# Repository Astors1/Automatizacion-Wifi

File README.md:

# Automatizacion wifi
Proyecto: Automatizaación WIFI Y infrarrojo. Alumnos: Alliana Facundo y Agustin Astorga ,con colaboracion de Alejo Guerra. Profesor: Martin Leguizamon. *Descripción del proyecto: Este dispositivo actúa como un control de tomacorrientes, donde se pueden agregar diferentes dispositivos, y permite apagarlos o prenderlos mediante una página web con interruptores. Además, cuenta con un sistema de control de seguridad (solo se puede activar manualmente)por infrarrojo, en caso de que no sea posible conectarse por WiFi. Objetivo: El objetivo principal es mejorar el control de dispositivos (luces, herramientas, etc.) de manera más práctica y permitir su manejo a distancia. En versiones anteriores, este dispositivo funcionaba mediante Bluetooth, lo que presentaba varias limitaciones: un alcance de solo 1 metro y la necesidad de instalar una aplicación en el teléfono móvil para su uso. En esta nueva versión, se mejorará la conexión a través de WiFi, lo que permitirá un mayor alcance y eliminará la necesidad de instalar aplicaciones adicionales, ya que funcionará mediante una dirección IP. Sin embargo, para situaciones en las que no se disponga de WiFi, el dispositivo contará con una opción de control por infrarrojos, que se podrá activar manualmente. Esta opción tendrá un alcance más limitado, pero ofrecerá una solución práctica y segura para su control. Listado de materiales/fuentes: • Microcontrolador ESP32/ (embebido reciclado) • Resistencias/optocopladores /transistores/pulsadores/rectificadores, etc (reciclados) • Relays x4 (reciclados) • Módulo infrarrojo (emisor/transmisor) ($8.000) • placa cobre doble faz (ya comprada) • Estaño, conectores, cables, etc ($10.000) Costo aproximado: $20.000.

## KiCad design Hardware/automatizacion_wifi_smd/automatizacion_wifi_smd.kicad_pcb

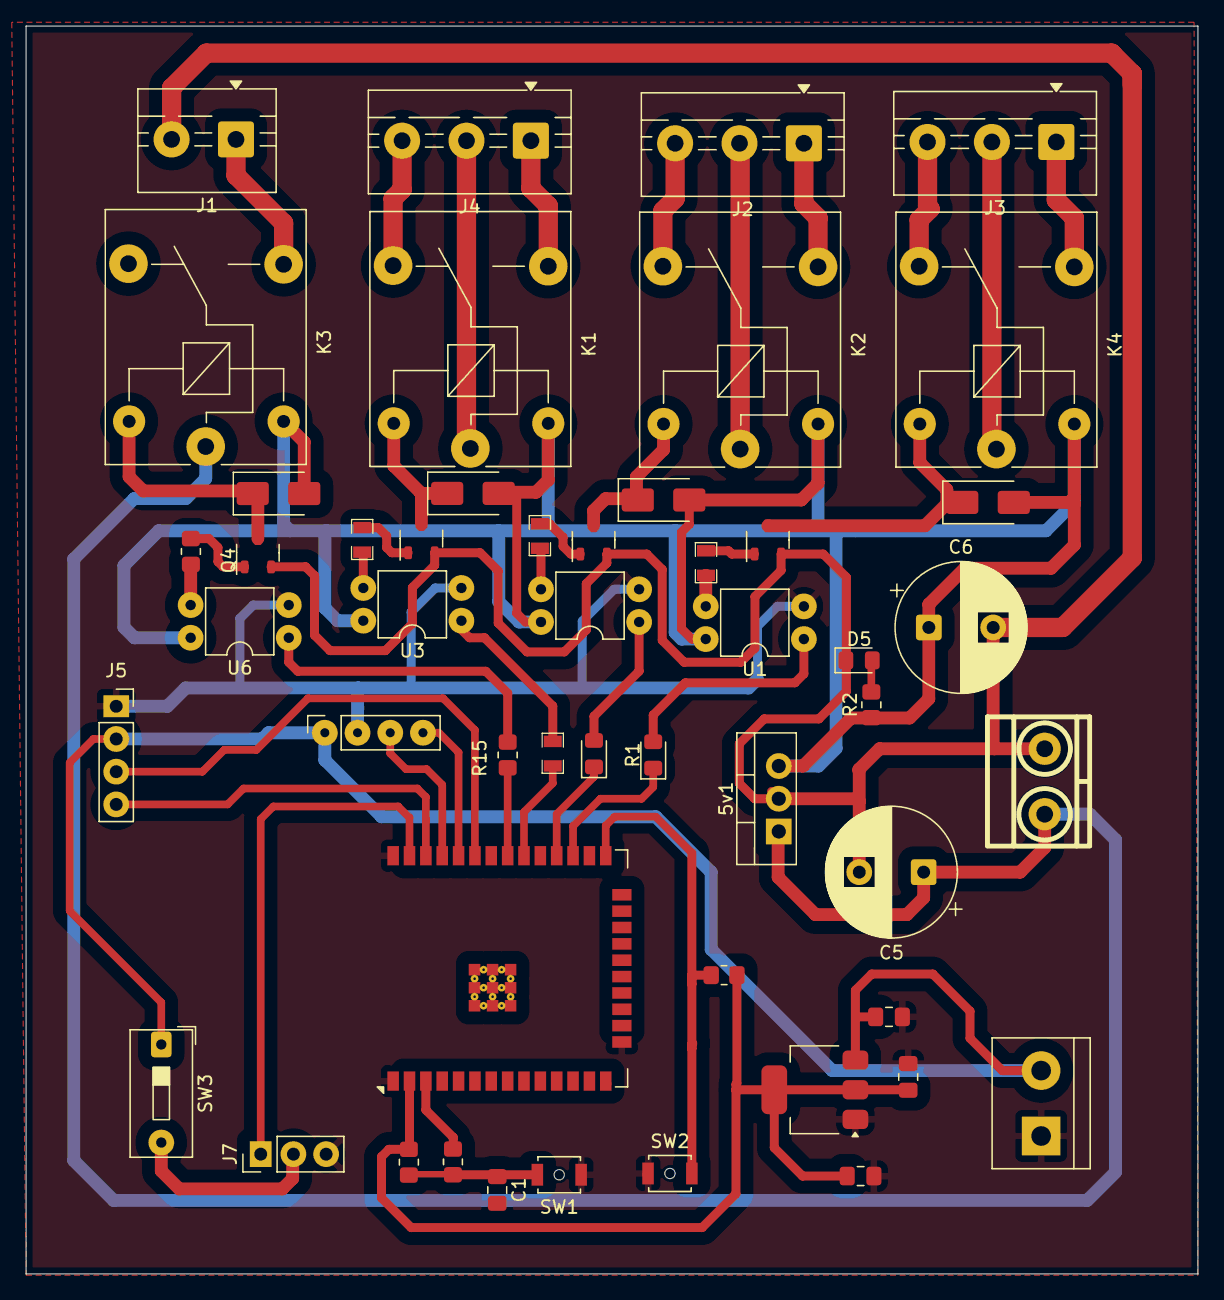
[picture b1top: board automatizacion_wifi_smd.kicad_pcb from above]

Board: 2 copper layers, 91.0 x 96.9 mm, 50 parts (0 on the bottom side), 46 nets.

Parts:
5v1: LM7805_TO220; TO-220-3_Vertical
C1: 100nF; C_0805_2012Metric_Pad1.18x1.45mm_HandSolder
C2, C4: 10 uF; C_0805_2012Metric_Pad1.18x1.45mm_HandSolder
C3: 100 nF; C_0805_2012Metric_Pad1.18x1.45mm_HandSolder
C5, C6: 100uf; CP_Radial_D10.0mm_P5.00mm
D1, D2, D3, D4: DIODE; D_SMA
D5: LED; LED_0805_2012Metric_Pad1.15x1.40mm_HandSolder
J1: Screw_Terminal_01x02; TerminalBlock_MaiXu_MX126-5.0-02P_1x02_P5.00mm
J2, J3, J4: Screw_Terminal_01x03; TerminalBlock_MaiXu_MX126-5.0-03P_1x03_P5.00mm
J5, J6: Conn_01x04_Pin; PinSocket_1x04_P2.54mm_Vertical
J7: Conn_01x03_Pin; PinHeader_1x03_P2.54mm_Vertical
K1, K2, K3, K4: RELAY_C; Relay_SPDT_SANYOU_SRD_Series_Form_C
Q1, Q2, Q3, Q4: 2N3904; P200_SOT-23
R1, R4: R; LED_0805_2012Metric_Pad1.15x1.40mm_HandSolder
R2: 2.2k; R_0805_2012Metric_Pad1.20x1.40mm_HandSolder
R3, R6, R9: R; R_0805
R7: 1k; R_0805
R10, R11, R12: 10K; R_0805_2012Metric_Pad1.20x1.40mm_HandSolder
R15, R17: R; R_0805_2012Metric_Pad1.20x1.40mm_HandSolder
SW1, SW2: SW_Push; SW_SPST_B3U-1000P-B
SW3: SW_SPST; SW_DIP_SPSTx01_Slide_9.78x4.72mm_W7.62mm_P2.54mm
U1, U2, U3, U6: PC817; DIP-4_W7.62mm
U4: ESP32-WROOM-32E__4MB_; ESP32-WROOM-32E
U5: NCP1117-1.5_SOT223; SOT-223-3_TabPin2
bornera1: bornera; BORNERA2_AZUL
bornera2: bornera; TerminalBlock_bornier-2_P5.08mm

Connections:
/3.3V: C3.2, C4.1, R10.1, R11.1, U4.2 (3V3), U5.2 (VO)
/5V: 5v1.3 (VO), C6.1, D1.2 (K), D2.2 (K), D3.2 (K), D4.2 (K), K1.2, K2.2, K3.2, K4.2, R2.1, U1.4, U2.4, U3.4, U6.4
/5VES: C2.1, J5.2, J6.1, SW3.1 (A), U5.3 (VI), bornera2.2
/C1: J4.2, K1.1
/C2: J3.2, K4.1
/C3: J2.2, K2.1
/EN: R12.2, U4.3 (EN)
/FLASH: R11.2, SW2.2, U4.25 (IO0)
/GNDE: C1.2, C2.2, C3.1, C4.2, J5.1, J6.2, J7.3, SW1.1, SW2.1, U1.2, U2.2, U3.2, U4.1 (GND), U4.15 (GND), U4.38 (GND), U5.1 (GND), U6.2, bornera2.1
/NC1: J4.3, K1.4
/NC2: J3.3, K4.4
/NC3: J2.3, K2.4
/NO1: J4.1, K1.3
/NO2: J3.1, K4.3
/NO3: J2.1, K2.3
/NO4: J1.1, K3.3
/R1: R7.1, U4.30 (IO18)
/R2: R1.1, U4.27 (IO16)
/R3: R4.1, U4.28 (IO17)
/R4: R15.1, U4.31 (IO19)
/RX: J6.4, U4.34 (RXD0)
/S: J7.1, U4.37 (IO23)
/SCL: J5.4, U4.36 (IO22)
/SDA: J5.3, U4.33 (IO21)
/SWITCH: C1.1, R10.2, R12.1, SW1.2
/TX: J6.3, U4.35 (TXD0)
/VIN: C5.1, K3.1, bornera1.1
GND: 5v1.2 (GND), C5.2, C6.2, D5.1 (K), J1.2, Q1.2 (E), Q2.2 (E), Q3.2 (E), Q4.2 (E), bornera1.2
unnamed: D1.1 (A), K4.5, Q3.3 (C)
unnamed: D2.1 (A), K2.5, Q2.3 (C)
unnamed: D3.1 (A), K1.5, Q1.3 (C)
unnamed: D4.1 (A), K3.5, Q4.3 (C)
unnamed: D5.2 (A), R2.2
unnamed: J7.2, SW3.2 (B)
unnamed: Q1.1 (B), R9.2
unnamed: Q2.1 (B), R6.2
unnamed: Q3.1 (B), R3.2
unnamed: Q4.1 (B), R17.2
unnamed: R1.2, U1.1
unnamed: R3.1, U1.3
unnamed: R4.2, U2.1
unnamed: R6.1, U2.3
unnamed: R7.2, U3.1
unnamed: R9.1, U3.3
unnamed: R15.2, U6.1
unnamed: R17.1, U6.3

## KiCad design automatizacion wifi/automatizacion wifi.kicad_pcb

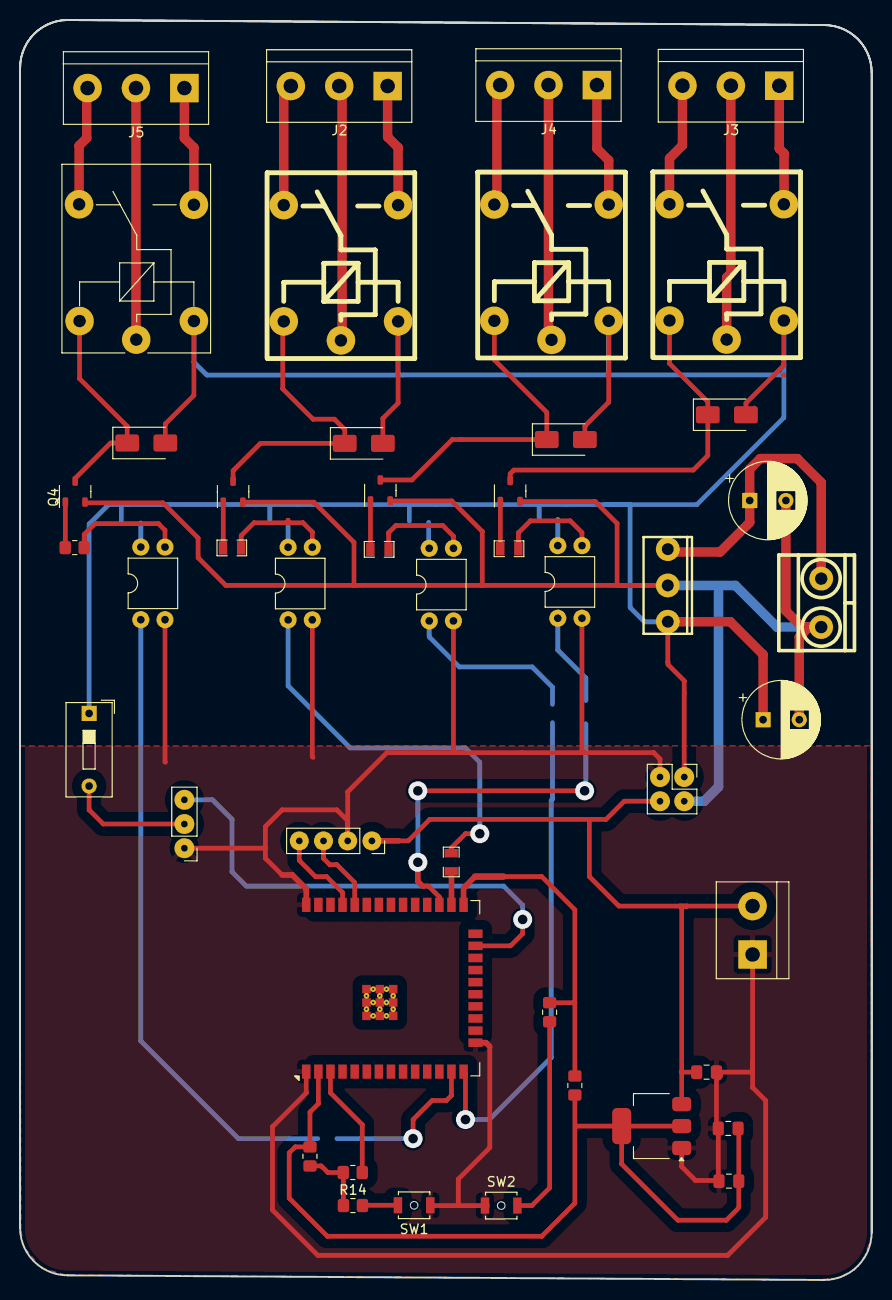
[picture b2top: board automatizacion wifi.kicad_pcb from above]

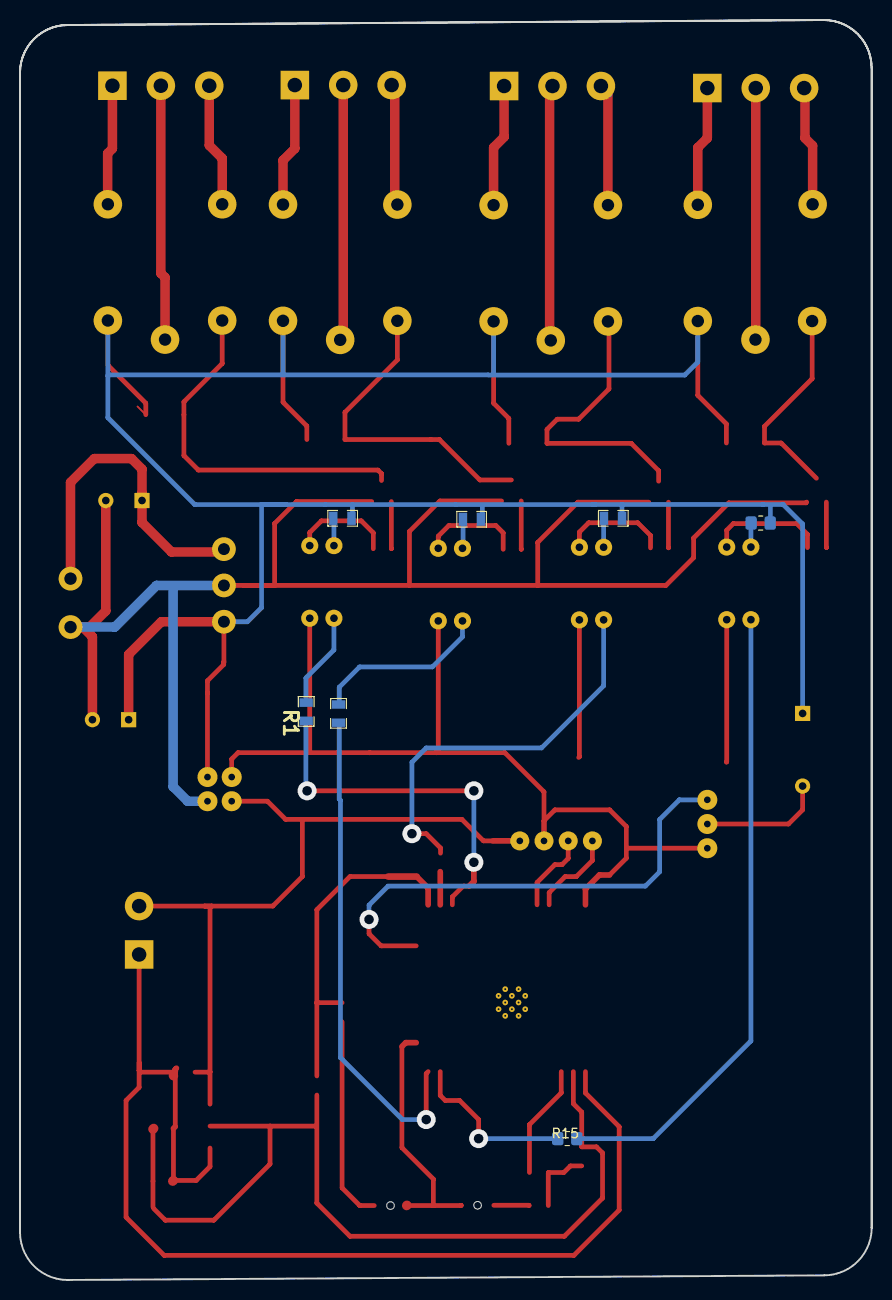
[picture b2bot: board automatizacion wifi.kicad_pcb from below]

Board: 2 copper layers, 89.4 x 132.2 mm, 53 parts (7 on the bottom side), 51 nets.

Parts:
5v1: LM7805_TO220; TO-220-2
C2, C4: 10 uF; C_0805_2012Metric_Pad1.18x1.45mm_HandSolder
C3: 100 nF; C_0805_2012Metric_Pad1.18x1.45mm_HandSolder
C5, C6: 100uf; CP_Radial_D8.0mm_P3.80mm
D1, D2, D3, D4: DIODE; D_SMA
J1: Conn_02x02_Counter_Clockwise; PinHeader_2x02_P2.54mm_Vertical
J2, J3, J4, J5: Screw_Terminal_01x03; TerminalBlock_bornier-3_P5.08mm
J6: Conn_01x04_Pin; PinSocket_1x04_P2.54mm_Vertical
J7: Screw_Terminal_01x03; PinHeader_1x03_P2.54mm_Vertical
K1, K2, K3: RELAY_C; Relay_C
K4: RELAY_C; Relay_SPDT_SANYOU_SRD_Series_Form_C
Q1, Q2, Q3, Q4: 2N3904; P200_SOT-23
R1, R2, R3, R4, R5, R6, R8, R9: R; R_0805
R7: 1k; R_0805
R10, R11, R12: 10K; R_0805_2012Metric_Pad1.20x1.40mm_HandSolder
R13, R14: 470; R_0805_2012Metric_Pad1.20x1.40mm_HandSolder
R15, R16, R17: R; R_0805_2012Metric_Pad1.20x1.40mm_HandSolder
SW1, SW2: SW_Push; SW_SPST_B3U-1000P-B
SW3: SW_SPST; SW_DIP_SPSTx01_Slide_9.78x4.72mm_W7.62mm_P2.54mm
U1, U2, U3, U6: PC817; DIP-4_W7.62mm
U4: ESP32-WROOM-32E__4MB_; ESP32-WROOM-32E
U5: NCP1117-1.5_SOT223; SOT-223-3_TabPin2
bornera1: bornera; BORNERA2_AZUL
bornera2: bornera; TerminalBlock_bornier-2_P5.08mm

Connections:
/3.3V: C3.2, C4.1, R10.1, R11.1, U4.2 (3V3), U5.2 (VO)
/5V: 5v1.3 (VO), C6.1, D1.2 (K), D2.2 (K), D3.2 (K), D4.2 (K), J1.1, K1.2, K2.2, K3.2, K4.2, R2.2, R5.1, R8.2, R16.2, SW3.1 (A)
/5VES: C2.1, J1.4, J6.1, U5.3 (VI), bornera2.2
/C1: J2.2, K3.1
/C2: J3.2, K1.1
/C3: J4.2, K2.1
/C4: J5.2, K4.1
/EN: R12.2, U4.3 (EN)
/FLASH: R11.2, R13.1, U4.25 (IO0)
/GNDE: C2.2, C3.1, C4.2, J1.3, J6.2, J7.1, SW1.1, SW2.1, U1.2, U2.2, U3.2, U4.1 (GND), U4.15 (GND), U4.38 (GND), U5.1 (GND), U6.2, bornera2.1
/NC1: J2.3, K3.4
/NC2: J3.3, K1.4
/NC3: J4.3, K2.4
/NC4: J5.3, K4.4
/NO1: J2.1, K3.3
/NO2: J3.1, K1.3
/NO3: J4.1, K2.3
/NO4: J5.1, K4.3
/R1: R7.1, U4.26 (IO4)
/R2: R1.1, U4.27 (IO16)
/R3: R4.1, U4.14 (IO12)
/R4: R15.1, U4.13 (IO14)
/RX: J6.3, U4.34 (RXD0)
/SWITCH: R10.2, R12.1, R14.1
/TX: J6.4, U4.35 (TXD0)
/VIN: 5v1.1 (VI), C5.1, bornera1.2
/s: J7.3, U4.23 (IO15)
GND: 5v1.2 (GND), C5.2, C6.2, J1.2, Q1.2 (E), Q2.2 (E), Q3.2 (E), Q4.2 (E), bornera1.1
unnamed: D1.1 (A), K1.5, Q3.3 (C)
unnamed: D2.1 (A), K2.5, Q2.3 (C)
unnamed: D3.1 (A), K3.5, Q1.3 (C)
unnamed: D4.1 (A), K4.5, Q4.3 (C)
unnamed: J7.2, SW3.2 (B)
unnamed: Q1.1 (B), R9.2
unnamed: Q2.1 (B), R6.2
unnamed: Q3.1 (B), R3.2
unnamed: Q4.1 (B), R17.2
unnamed: R1.2, U1.1
unnamed: R2.1, U1.4
unnamed: R3.1, U1.3
unnamed: R4.2, U2.1
unnamed: R5.2, U2.4
unnamed: R6.1, U2.3
unnamed: R7.2, U3.1
unnamed: R8.1, U3.4
unnamed: R9.1, U3.3
unnamed: R13.2, SW2.2
unnamed: R14.2, SW1.2
unnamed: R15.2, U6.1
unnamed: R16.1, U6.4
unnamed: R17.1, U6.3
